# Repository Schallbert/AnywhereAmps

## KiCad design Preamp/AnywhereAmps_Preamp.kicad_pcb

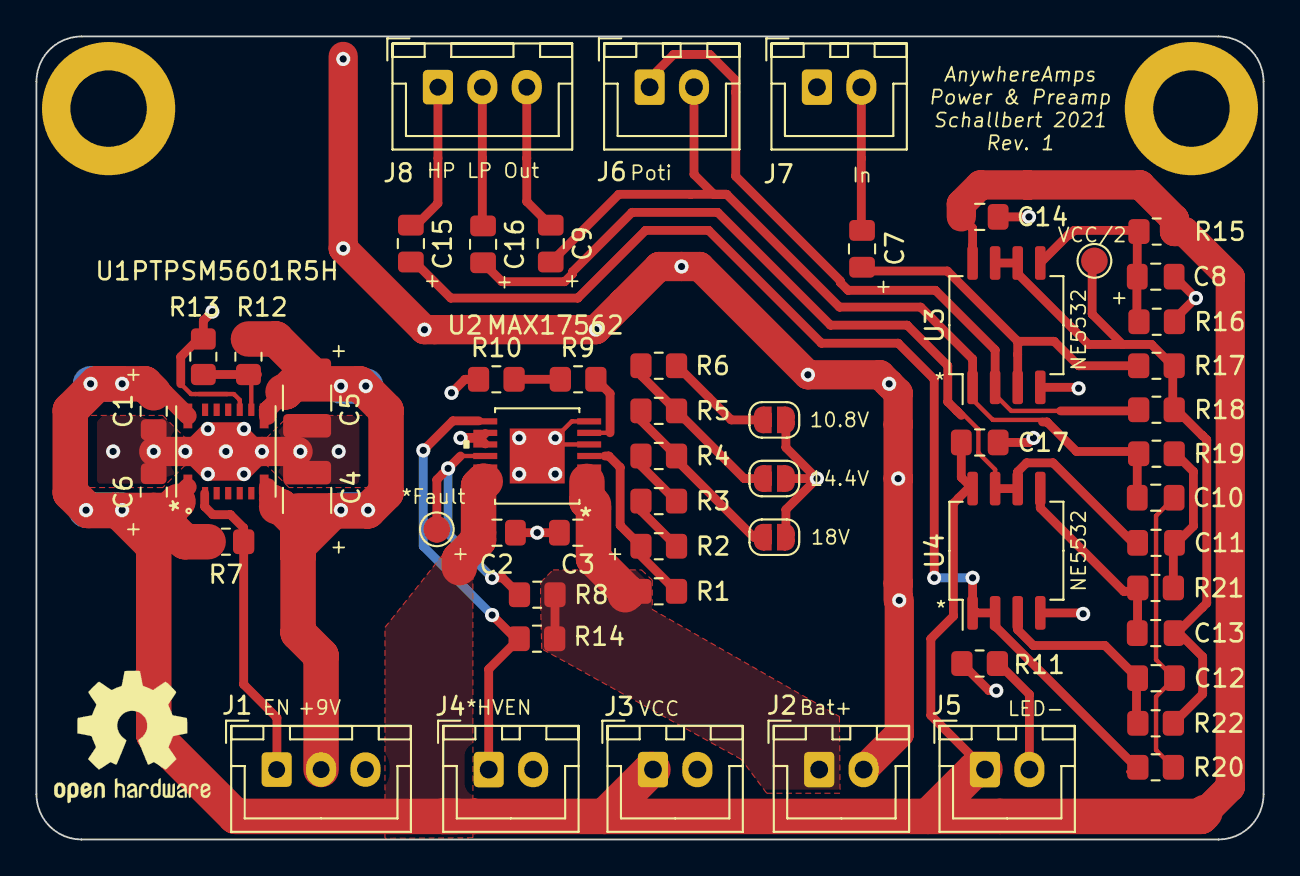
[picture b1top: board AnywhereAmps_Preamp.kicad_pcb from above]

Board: 2 copper layers, 69.1 x 45.2 mm, 56 parts (0 on the bottom side), 32 nets.

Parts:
C1, C2, C3, C6, C7, C8, C9, C15, C16: 4.7u; C_0805_2012Metric_Pad1.18x1.45mm_HandSolder
C4, C5: 47u; C_1210_3225Metric_Pad1.33x2.70mm_HandSolder
C10, C11, C12, C13, C14, C17: 33n; C_0805_2012Metric_Pad1.18x1.45mm_HandSolder
J1: +9V; JST_XH_B3B-XH-A_1x03_P2.50mm_Vertical
J2: Battery; JST_XH_B2B-XH-A_1x02_P2.50mm_Vertical
J3: VCC; JST_XH_B2B-XH-A_1x02_P2.50mm_Vertical
J4: Switch; JST_XH_B2B-XH-A_1x02_P2.50mm_Vertical
J5: Pwr LED; JST_XH_B2B-XH-A_1x02_P2.50mm_Vertical
J6: POTI; JST_XH_B2B-XH-A_1x02_P2.50mm_Vertical
J7: Audio_In; JST_XH_B2B-XH-A_1x02_P2.50mm_Vertical
J8: Audio_Out; JST_XH_B3B-XH-A_1x03_P2.50mm_Vertical
JP1: 18V; SolderJumper-2_P1.3mm_Open_RoundedPad1.0x1.5mm
JP2: 14.4V; SolderJumper-2_P1.3mm_Open_RoundedPad1.0x1.5mm
JP3: 10.8V; SolderJumper-2_P1.3mm_Open_RoundedPad1.0x1.5mm
R1, R7, R8, R14: 390k; R_0805_2012Metric_Pad1.20x1.40mm_HandSolder
R2, R3, R4, R5, R6, R12, R15, R16, R17, R18, R19, R20, R21, R22: 10k; R_0805_2012Metric_Pad1.20x1.40mm_HandSolder
R9, R10, R11, R13: 1.2k; R_0805_2012Metric_Pad1.20x1.40mm_HandSolder
TP1: *Fault; TestPoint_Pad_D1.5mm
TP2: TestPoint; TestPoint_Pad_D1.5mm
U1: PTPSM5601R5H; PTPSM5601R5HRDAR
U2: MAX17562; MAX17562AUD&plus_
U3, U4: NE5532; SO-8_5.3x6.2mm_P1.27mm

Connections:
*FLAG: R8.2, TP1.1, U2.11
*HVEN: J4.1, R14.1, U2.8
+9V: C4.1, C5.1, J1.2, R12.1, U1.7, U1.8
+BATT: C3.1, J2.1, R1.2, R8.1, R14.2, U2.1, U2.2, U2.3
AudioIn: C7.2, J7.2
AudioOut: C9.2, J8.3
EN: J1.1, R7.1, U1.2
FB: R12.2, R13.1, U1.9
GND: C1.2, C2.2, C3.2, C4.2, C5.2, C6.2, C8.2, C14.2, C17.1, J1.3, J2.2, J3.2, J4.2, J7.1, JP1.2, JP2.2, JP3.2, R10.1, R11.1, R13.2, R16.1, U1.10, U1.15, U2.5, U2.7, U2.9, U2.10, U2.EPAD, U3.4, U4.4
GNDA: C13.1, R17.2, R18.2, R22.2, TP2.1, U3.6, U3.7
HP_Out: C15.2, J8.1
LP_Out: C16.2, J8.2
unnamed: C7.1, R17.1, U3.3
unnamed: C8.1, R15.1, R16.2, U3.5
unnamed: C10.1, C12.2, R20.1
unnamed: C11.1, C16.1, U4.6, U4.7
unnamed: C11.2, R19.1, R21.2
unnamed: C12.1, R22.1, U4.3
unnamed: C13.2, R21.1, U4.5
unnamed: C15.1, R20.2, U4.1, U4.2
unnamed: J5.2, R11.2
unnamed: JP1.1, R4.2, R5.1
unnamed: JP2.1, R5.2, R6.1
unnamed: JP3.1, R6.2
unnamed: R2.2, R3.2
unnamed: R3.1, R4.1
unnamed: R9.1, R10.2
Poti: J6.1, R18.1, U3.2
PreampOut: C9.1, C10.2, J6.2, R19.2, U3.1
SETI: R9.2, U2.6
UVLO: R1.1, R2.1, U2.4
VCC: C1.1, C2.1, C6.1, C14.1, C17.2, J3.1, J5.1, R7.2, R15.2, U1.1, U1.14, U2.12, U2.13, U2.14, U3.8, U4.8

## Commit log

2021-09-23 add OSHW logo
2021-09-24 - increate power track size to 2mm - reduce amount of right angles in track design
2021-09-24 - more 45° edging - update silk screen
2021-09-25 - switch to polarized capacitors for audio input - increase cap size for bypass on 9V rail - add polarity indicator on silk screen
2021-09-26 - move VCC track away from M4 hole - exchange 383k resistors by E12 390k - use 10k resistors for VGND providers (quicker startup)
2021-09-27 - update pullup for 9V supply: Now, barrel GND is outer. - fix review findings (track spacing)
2021-10-02 - Change from EH to XH connectors, vertical - Re-align and place connectors - Delete LED, use TestPoint instead - Optimize 2mm tracks for shortness - update BOM
2021-10-02 - improve via'd tracks - fix silkscreen items
2021-10-03 - minor SilkScreen placement fixes
2021-10-03 - fine-tune component placement - add batt and VCC copper layers - update SilkScreen
2021-10-03 - update 1.25k resistors to 1.2k resistors
2021-10-20 Init commit for freecad project
2021-10-26 1st template for milling
2021-10-26 Arrange milling template for better usage of Nutzen
2021-10-28 update Nutzen to 480 * 600
2021-10-30 add baffle dia file add holes to 3d sketches
2021-11-01 Finalize holes Arrange for 400x700 Nutzen REV1 - added STL
2021-11-01 add dxf Issues: - Top and Bottom (big round parts) don't extrude OK
2021-11-05 add logos to solution /2D update Max1756c calculation update 3D data for CNC
2021-11-19 add variant vor PassiveRadiator to Alpha
2021-11-20 complete drawings for Alpha1.2
2021-11-24 - finalize CAM - add classic drawing for TOP - recalculate VUVLO for new 1.2 schematics
2021-12-04 Redesign max1756x application calculator
2022-03-20 Update AnywhereAmps Alpha 3d CAD data. Add AnywhereAmps logo for CAD.
2022-04-01 update CAD data to reflect latest prototyping corrections Move all speakercarriers to one stl
2022-07-08 Various updates to AnywhereAmps design, and most of its files.
2022-07-08 remove breaking 3D renderings reason: high maintenance effort without benefit

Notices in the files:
parts and their libraries:
Copyright 2021 Accelerated Designs. All rights reserved.
